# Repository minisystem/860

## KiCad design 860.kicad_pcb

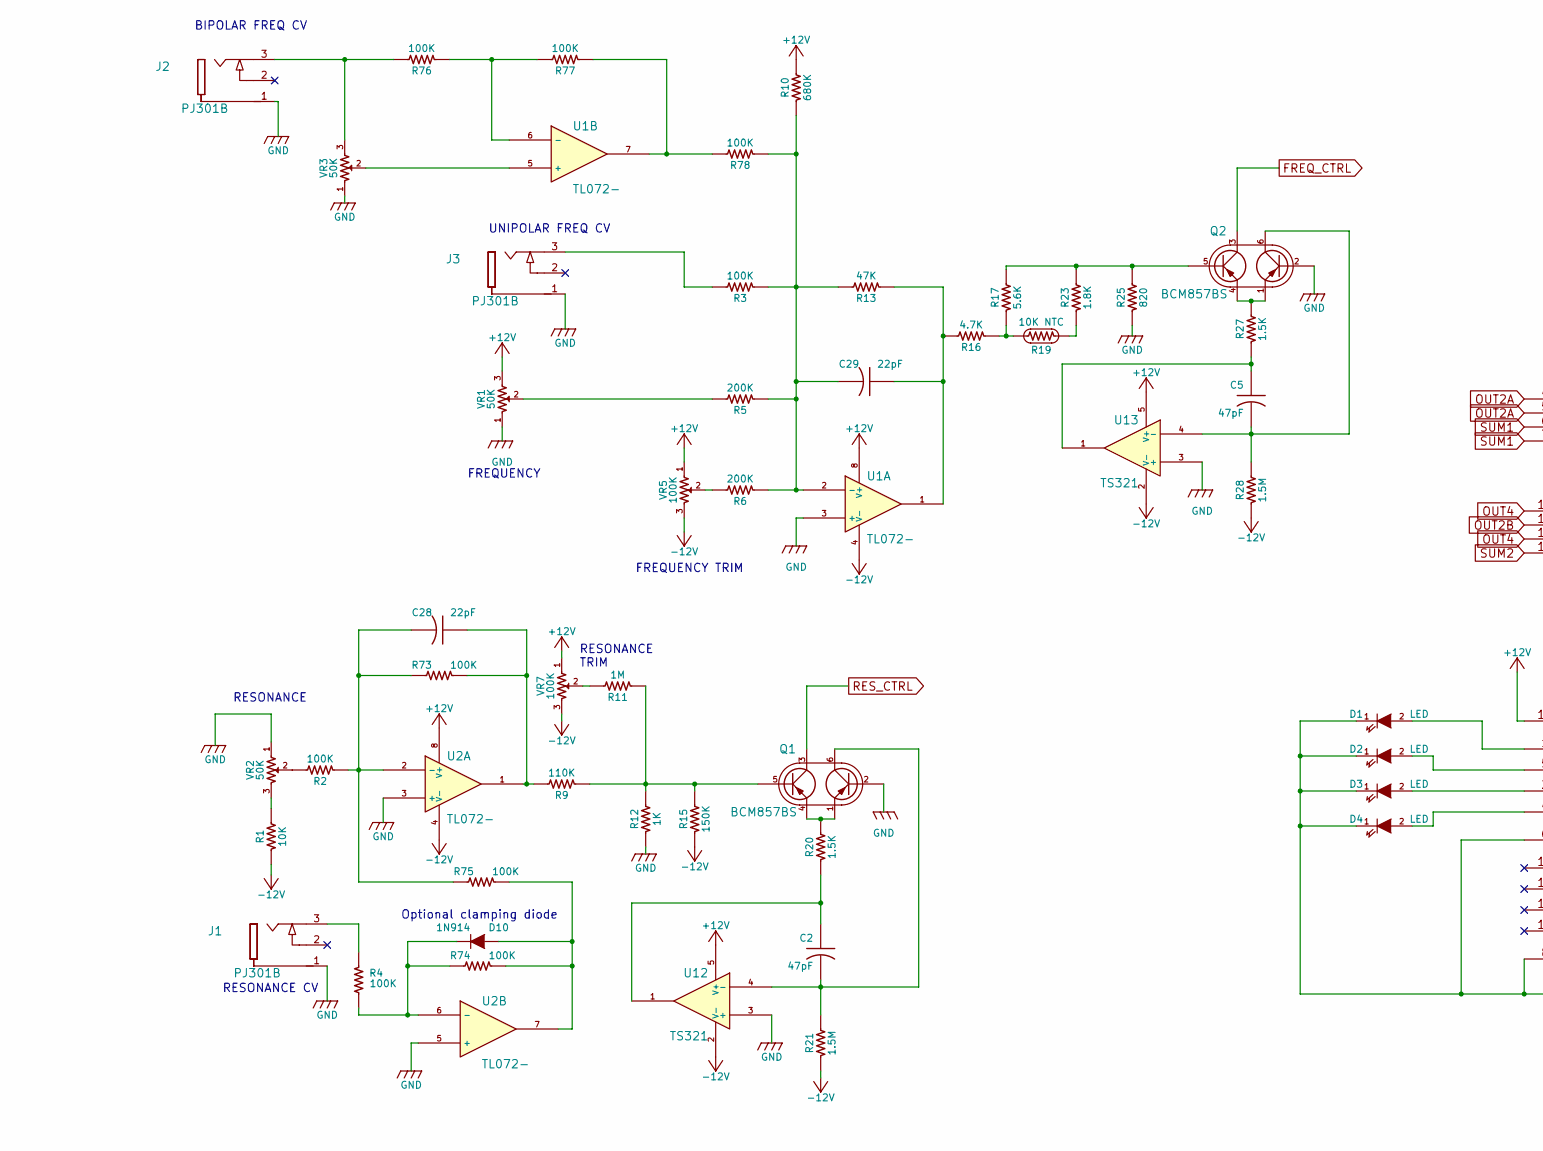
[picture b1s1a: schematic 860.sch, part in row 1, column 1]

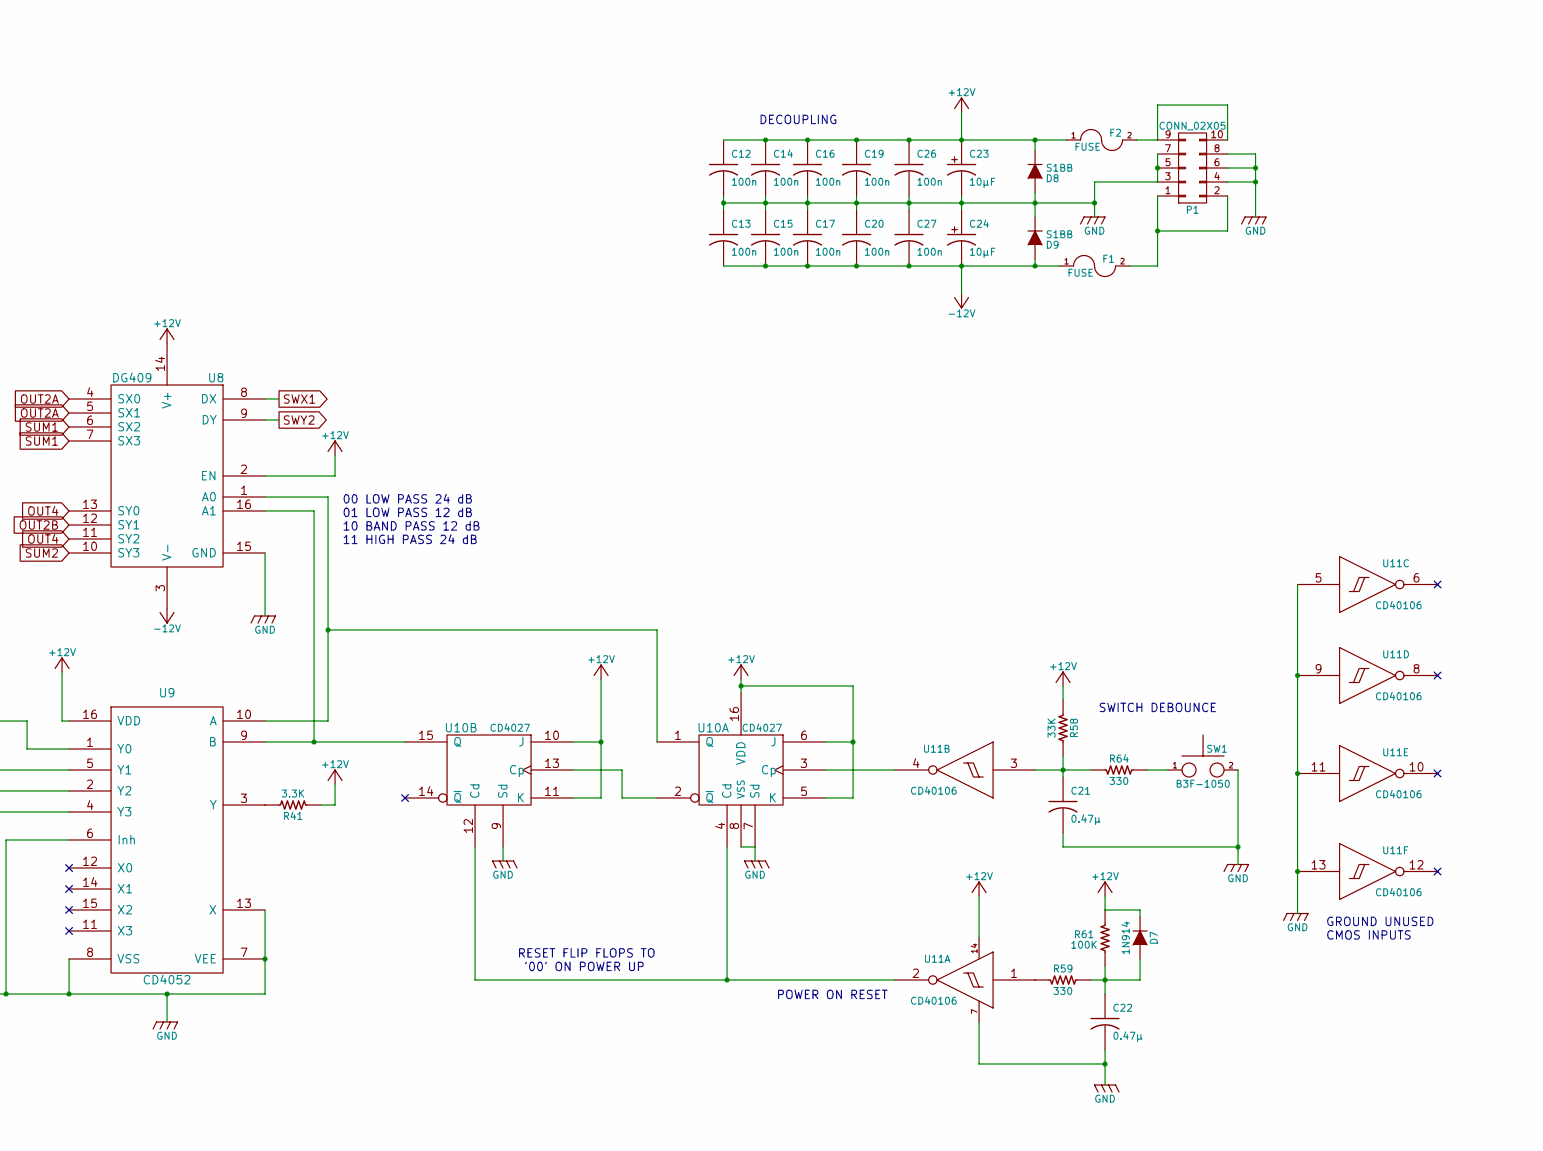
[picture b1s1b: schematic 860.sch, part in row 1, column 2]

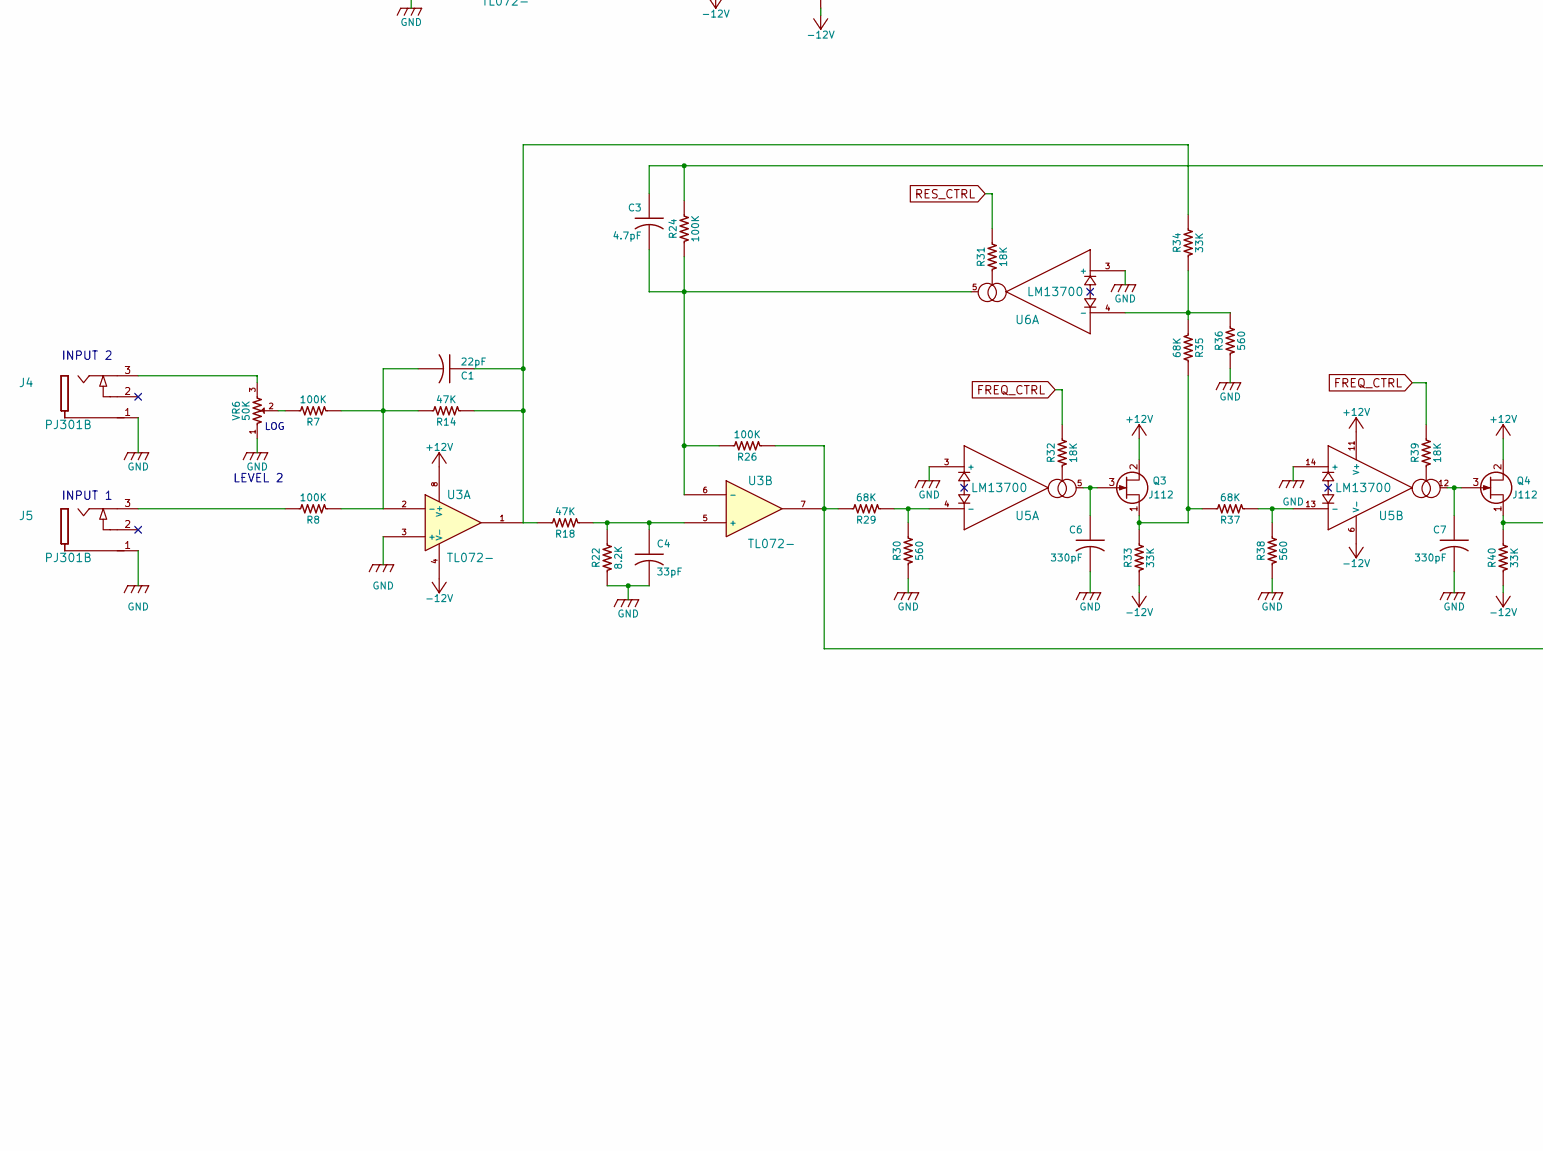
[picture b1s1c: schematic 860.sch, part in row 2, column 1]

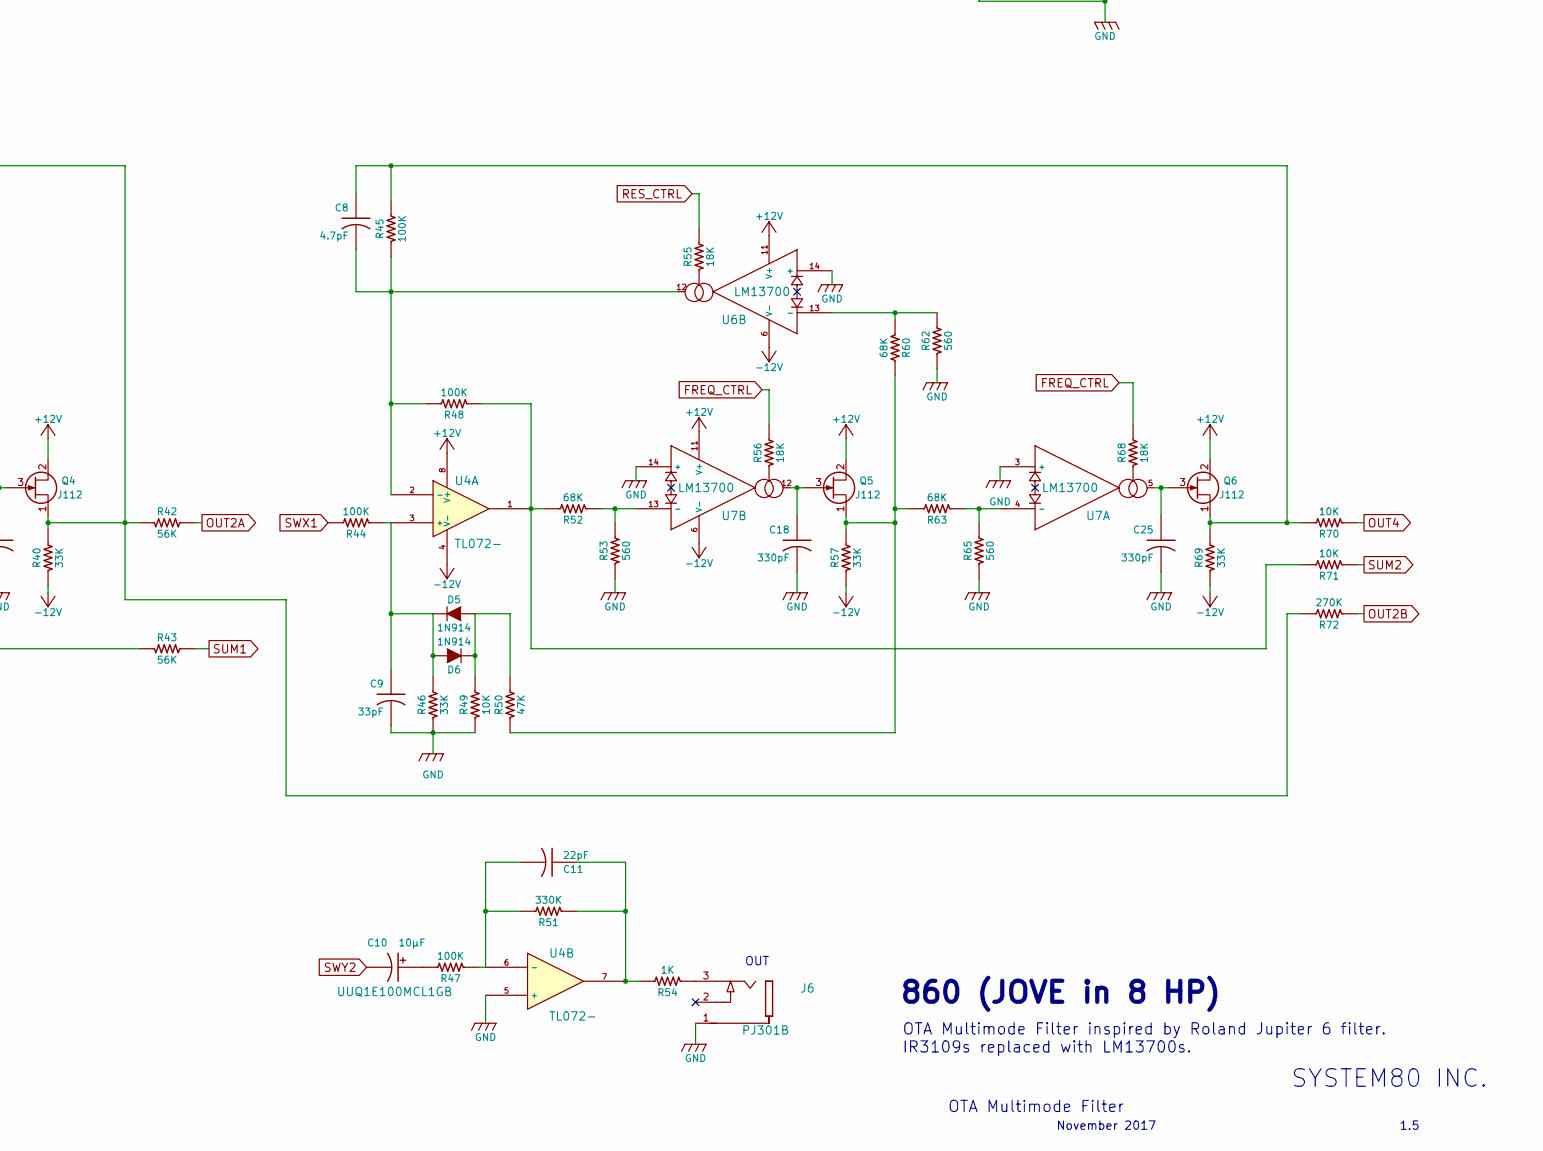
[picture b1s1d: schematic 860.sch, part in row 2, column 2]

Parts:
C1, C11, C28, C29: 22pF; SM0603-C-JRL
C2, C5: 47pF; SM0603-C-JRL
C3, C8: 4.7pF; SM0603-C-JRL
C4, C9: 33pF; SM0603-C-JRL
C6, C7, C18, C25: 330pF; SM0805-HAND-C
C10: 10μF; jrl_c_elec_5x5.3; Part Number UUQ1E100MCL1GB
C12, C13, C14, C15, C16, C17, C19, C20, C26, C27: 100n; SM0603-C-JRL
C21, C22: 0.47μ; SM0603-C-JRL
C23, C24: 10μF; jrl_c_elec_5x5.3; Part Number UWJ1E100MCL1GB
D1, D2, D3, D4: LED; 3MM-LED-C1A2
D5, D6, D7, D10: 1N914; SOD323-C1A2
D8, D9: S1BB; SMB-1C2A
F1, F2: FUSE; SM0805-HAND
J1, J2, J3, J4, J5, J6: PJ301B; PJ-301B-JACK-SLOTS
P1: CONN_02X05; Pin_Header_Straight_2x05_Pitch2.54mm
Q1, Q2: BCM857BS; sot323-6
Q3, Q4, Q5, Q6: J112; SOT23-JRL
R1, R49, R70, R71: 10K; SM0603-R-JRL
R2, R3, R4, R7, R8, R24, R26, R44, R45, R47, R48, R61, R73, R74, R75, R76, R77, R78: 100K; SM0603-R-JRL
R5, R6: 200K; SM0603-R-JRL
R9: 110K; SM0603-R-JRL
R10: 680K; SM0603-R-JRL
R11: 1M; SM0603-R-JRL
R12, R54: 1K; SM0603-R-JRL
R13, R14, R18, R50: 47K; SM0603-R-JRL
R15: 150K; SM0603-R-JRL
R16: 4.7K; SM0603-R-JRL
R17: 5.6K; SM0603-R-JRL
R19: 10K NTC; SM0805-HAND
R20, R27: 1.5K; SM0603-R-JRL
R21, R28: 1.5M; SM0603-R-JRL
R22: 8.2K; SM0603-R-JRL
R23: 1.8K; SM0603-R-JRL
R25: 820; SM0603-R-JRL
R29, R35, R37, R52, R60, R63: 68K; SM0603-R-JRL
R30, R36, R38, R53, R62, R65: 560; SM0603-R-JRL
R31, R32, R39, R55, R56, R68: 18K; SM0603-R-JRL
R33, R34, R40, R46, R57, R58, R69: 33K; SM0603-R-JRL
R41: 3.3K; SM0603-R-JRL
R42, R43: 56K; SM0603-R-JRL
R51: 330K; SM0603-R-JRL
R59, R64: 330; SM0603-R-JRL
R72: 270K; SM0603-R-JRL
SW1: B3F-1050; B3F-1050-OMRON
U1, U2, U3, U4: TL072-; TSSOP8-JRL
U5, U6, U7: LM13700; SO16-JRL
U8: DG409; SO16-JRL
U9: CD4052; TSSOP-16_4.4x5mm_Pitch0.65mm
U10: CD4027; TSSOP-16_4.4x5mm_Pitch0.65mm
U11: CD40106; TSSOP-14_4.4x5mm_Pitch0.65mm
U12, U13: TS321; SOT-23-5
VR1, VR2, VR3: 50K; RD901F-ALPHA-POT-T18
VR5, VR7: 100K; TC33X-2
VR6: 50K; RV09AF-40-ALPHA-POT

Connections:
+12V: C12.1, C14.1, C16.1, C19.1, C23.1 (+), C26.1, D7.1 (K), D8.1 (K), F2.1, Q3.2 (D), Q4.2 (D), Q5.2 (D), Q6.2 (D), R10.2, R41.1, R58.2, R61.2, U1.8 (V+), U2.8 (V+), U3.8 (V+), U4.8 (V+), U5.11 (V+), U6.11 (V+), U7.11 (V+), U8.2 (EN), U8.14 (V+), U9.16 (VDD), U10.5 (K), U10.6 (J), U10.10 (J), U10.11 (K), U10.16 (VDD), U11.14 (VDD), U12.5 (V+), U13.5 (V+), VR1.3, VR5.1, VR7.1
-12V: C13.2, C15.2, C17.2, C20.2, C24.2 (-), C27.2, D9.2 (A), F1.1, R1.2, R15.2, R21.2, R28.2, R33.1, R40.1, R57.1, R69.1, U1.4 (V-), U2.4 (V-), U3.4 (V-), U4.4 (V-), U5.6 (V-), U6.6 (V-), U7.6 (V-), U8.3 (V-), U12.2 (V-), U13.2 (V-), VR5.3, VR7.3
FREQ_CTRL: Q2.3 (C2), R32.2, R39.2, R56.2, R68.2
GND: C4.2, C6.2, C7.2, C9.2, C12.2, C13.1, C14.2, C15.1, C16.2, C17.1, C18.2, C19.2, C20.1, C21.2, C22.2, C23.2 (-), C24.1 (+), C25.2, C26.2, C27.1, D1.1 (K), D2.1 (K), D3.1 (K), D4.1 (K), D8.2 (A), D9.1 (K), J1.1, J2.1, J3.1, J4.1, J5.1, J6.1, P1.3, P1.4, P1.5, P1.6, P1.7, P1.8, Q1.2 (B1), Q2.2 (B1), R12.2, R22.1, R25.1, R30.1, R36.1, R38.1, R46.1, R49.1, R53.1, R62.1, R65.1, SW1.2, U1.3 (+), U2.3 (+), U2.5 (+), U3.3 (+), U4.5 (+), U5.3 (+), U5.14 (+), U6.3 (+), U6.14 (+), U7.3 (+), U7.14 (+), U8.15 (GND), U9.6 (Inh), U9.7 (VEE), U9.8 (VSS), U9.13 (X), U10.7 (Sd), U10.8 (VSS), U10.9 (Sd), U11.5 (In), U11.7 (VSS), U11.9 (In), U11.11 (In), U11.13 (In), U12.3 (+), U13.3 (+), VR1.1, VR2.1, VR3.1, VR6.1
unnamed: C1.1, R14.1, R18.2, R34.2, U3.1
unnamed: C1.2, R7.1, R8.1, R14.2, U3.2 (-)
unnamed: C2.1, R20.2, U12.1
unnamed: C2.2, Q1.6 (C1), R21.1, U12.4 (-)
unnamed: C3.1, Q4.1 (S), R24.2, R40.2, R42.2, R72.2
unnamed: C3.2, R24.1, R26.2, U3.6 (-), U6.5
unnamed: C4.1, R18.1, R22.2, U3.5 (+)
unnamed: C5.1, R27.2, U13.1
unnamed: C5.2, Q2.6 (C1), R28.1, U13.4 (-)
unnamed: C6.1, Q3.3 (G), U5.5
unnamed: C7.1, Q4.3 (G), U5.12
unnamed: C8.1, Q6.1 (S), R45.2, R69.2, R70.2
unnamed: C8.2, R45.1, R48.2, U4.2 (-), U6.12
unnamed: C9.1, D5.1 (K), D6.2 (A), R44.1, R46.2, U4.3 (+)
unnamed: C10.1 (+), R47.2
unnamed: C11.1, R51.1, R54.2, U4.7
unnamed: C11.2, R47.1, R51.2, U4.6 (-)
unnamed: C18.1, Q5.3 (G), U7.12
unnamed: C21.1, R58.1, R64.1, U11.3 (In)
unnamed: C22.1, D7.2 (A), R59.2, R61.1
unnamed: C25.1, Q6.3 (G), U7.5
unnamed: C28.1, R9.2, R73.1, U2.1
unnamed: C28.2, R2.1, R73.2, R75.2, U2.2 (-)
unnamed: C29.1, R13.1, R16.2, U1.1
unnamed: C29.2, R3.1, R5.1, R6.1, R10.1, R13.2, R78.1, U1.2 (-)
unnamed: D1.2 (A), U9.1 (Y0)
unnamed: D2.2 (A), U9.5 (Y1)
unnamed: D3.2 (A), U9.2 (Y2)
unnamed: D4.2 (A), U9.4 (Y3)
unnamed: D5.2 (A), D6.1 (K), R49.2, R50.2
unnamed: D10.1 (K), R4.1, R74.2, U2.6 (-)
unnamed: D10.2 (A), R74.1, R75.1, U2.7
unnamed: F1.2, P1.1, P1.2
unnamed: F2.2, P1.9, P1.10
unnamed: J1.3, R4.2
unnamed: J2.3, R76.2, VR3.3
unnamed: J3.3, R3.2
unnamed: J4.3, VR6.3
unnamed: J5.3, R8.2
unnamed: J6.3, R54.1
unnamed: Q1.1 (E1), Q1.4 (E2), R20.1
unnamed: Q1.5 (B2), R9.1, R11.1, R12.1, R15.1
unnamed: Q2.1 (E1), Q2.4 (E2), R27.1
unnamed: Q2.5 (B2), R17.2, R23.2, R25.2
unnamed: Q3.1 (S), R33.2, R35.2, R37.2
unnamed: Q5.1 (S), R50.1, R57.2, R60.2, R63.2
unnamed: R1.1, VR2.3
unnamed: R2.2, VR2.2
unnamed: R5.2, VR1.2
unnamed: R6.2, VR5.2
unnamed: R7.2, VR6.2
unnamed: R11.2, VR7.2
unnamed: R16.1, R17.1, R19.2
unnamed: R19.1, R23.1
unnamed: R26.1, R29.2, R43.2, U3.7
unnamed: R29.1, R30.2, U5.4 (-)
unnamed: R31.1, U6.1
unnamed: R32.1, U5.1
unnamed: R34.1, R35.1, R36.2, U6.4 (-)
unnamed: R37.1, R38.2, U5.13 (-)
unnamed: R39.1, U5.16
unnamed: R41.2, U9.3 (Y)
unnamed: R48.1, R52.2, R71.2, U4.1
unnamed: R52.1, R53.2, U7.13 (-)
unnamed: R55.1, U6.16
unnamed: R56.1, U7.16
unnamed: R59.1, U11.1 (In)
unnamed: R60.1, R62.2, U6.13 (-)
unnamed: R63.1, R65.2, U7.4 (-)
unnamed: R64.2, SW1.1
unnamed: R68.1, U7.1
unnamed: R76.1, R77.2, U1.6 (-)
unnamed: R77.1, R78.2, U1.7
unnamed: U1.5 (+), VR3.2
unnamed: U8.1 (A0), U9.10 (A), U10.1 (Q)
unnamed: U10.3 (Cp), U11.4 (Out)
unnamed: U10.4 (Cd), U10.12 (Cd), U11.2 (Out)
unnamed: U10.2 (~Q), U10.13 (Cp)
unnamed: U8.16 (A1), U9.9 (B), U10.15 (Q)
OUT2A: R42.1, U8.4 (SX0), U8.5 (SX1)
OUT2B: R72.1, U8.12 (SY1)
OUT4: R70.1, U8.11 (SY2), U8.13 (SY0)
RES_CTRL: Q1.3 (C2), R31.2, R55.2
SUM1: R43.1, U8.6 (SX2), U8.7 (SX3)
SUM2: R71.1, U8.10 (SY3)
SWX1: R44.2, U8.8 (DX)
SWY2: C10.2 (-), U8.9 (DY)

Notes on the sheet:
00 LOW PASS 24 dB 01 LOW PASS 12 dB 10 BAND PASS 12 dB 11 HIGH PASS 24 dB
POWER ON RESET
SWITCH DEBOUNCE
DECOUPLING
GROUND UNUSED CMOS INPUTS
RESET FLIP FLOPS TO '00' ON POWER UP
LOG
FREQUENCY TRIM
FREQUENCY
RESONANCE
BIPOLAR FREQ CV
RESONANCE CV
RESONANCE TRIM
UNIPOLAR FREQ CV
Optional clamping diode
INPUT 2
LEVEL 2
INPUT 1
OTA Multimode Filter
1.5
OUT
November 2017
OTA Multimode Filter inspired by Roland Jupiter 6 filter. IR3109s replaced with LM13700s.
860 (JOVE in 8 HP)
SYSTEM80 INC.

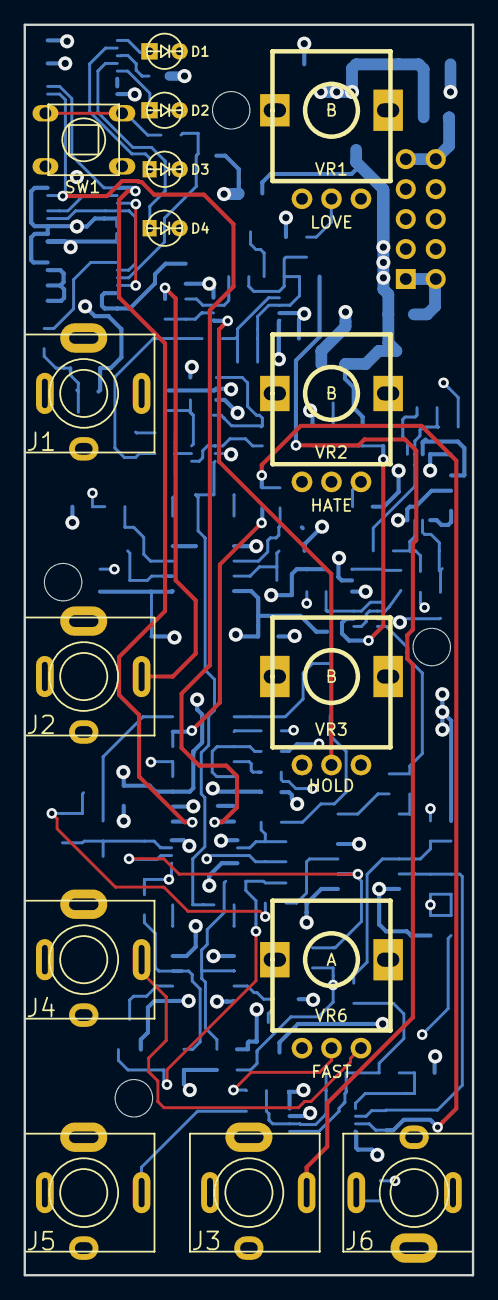
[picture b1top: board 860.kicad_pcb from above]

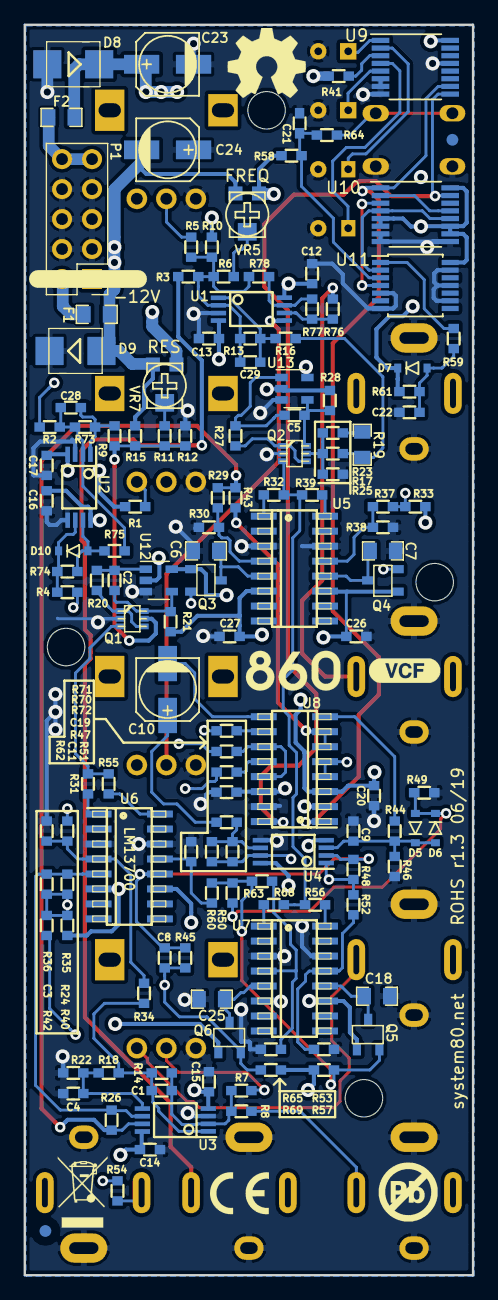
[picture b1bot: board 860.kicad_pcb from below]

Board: 4 copper layers, 38.0 x 106.0 mm, 154 parts (135 on the bottom side), 91 nets.

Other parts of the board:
SNAP-HOLE-0.125-INCH, SNAP-HOLE-0.125-INCH#2, SNAP-HOLE-0.125-INCH#3, SNAP-HOLE-0.125-INCH#4: VAL**; SNAP_HOLE_0.125_INCH

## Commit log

2017-11-26 routed, silk screen adjusted
2017-11-26 getting pretty close to done
2018-02-08 front component adjustments to jive with panel template
2018-02-09 tweaked routing to improve ground plane
2019-05-10 fixed hardware placement to match panel mechanical, moving power header
2019-05-11 updated 0603 footprints for production, new hole centres for aligning with panel holes
2019-06-04 added backplane and corresponding snap holes
2019-06-05 working on backplane, DRC done on 860 PCB
2019-06-08 silk screen adjust on 860 PCB, alignment check of backplane: OK
2019-06-08 alignment to front panel sample: OK
2019-06-12 ordered next revision PCB for testing, fitting, added backplane
2019-06-25 silk screen fiddling before panelization
2019-06-26 panelization
2019-08-24 updating user guide, fabrication outputs for pick and place
